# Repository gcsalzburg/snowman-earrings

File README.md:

# ⛄ Snowman Earrings

An experiment in using the ATtiny85 and ISP programming.

## Design

| Pin | Function | Programming |
| --- | --- | --- |
| 0 | Push switch | MOSI |
| 1 | Left eye | MISO |
| 2 | Right eye | SCK |
| 3 | Inner mouth | - |
| 4 | Outer mouth | - |
| 5 | - | RST |

The nose LED is connected permanently to power supply.

+ Micro = [ATTINY85-20SU](https://www.mouser.co.uk/ProductDetail/microchip/attiny85-20su/?qs=8jWQYweyg6N%2FGXnwAe4Icw==&countrycode=DE&currencycode=EUR) 
+ LED = [Broadcom HSMA-C170-T0000](https://www.mouser.co.uk/ProductDetail/broadcom-limited/hsma-c170-t0000/?qs=tMOYG%252bw4%252bLzJIEVH84X7hQ==&countrycode=DE&currencycode=EUR)
+ Switch = [Omron B3U-1000P](https://www.mouser.co.uk/ProductDetail/omron/b3u-1000p/?qs=AO7BQMcsEu4ip80xyf2FwA==&countrycode=DE&currencycode=EUR)
+ Battery holder = [Keystone 3002](https://www.mouser.co.uk/ProductDetail/keystone-electronics/3002/?qs=Mn60vILZNNZWJpgHXc3g8Q==&countrycode=DE&currencycode=EUR)  
+ Power supply = CR2032 battery

## How to program

1. Upload the sketch `File > Examples > 11.ArduinoISP > ArduinoISP` to Arduino Uno.
2. Wire up UNO as shown below:

   | What | Uno | ATtiny85 |
   | --- | --- | --- |
   | 5V  | Vcc | Vcc |
   | Gnd | Gnd | Gnd |
   | SCK | Pin 13 | Pin 2 |
   | MISO | Pin 13 | Pin 1 |
   | MOSI | Pin 13 | Pin 0 |
   | RST | Pin 13 | Reset |

	Also add a 10μF capacitor between Uno RESET and GND, to avoid Arduino being auto reset when uploading to ATtiny85. This goes in backwards (i.e. anode of capacitor is in GND of Uno).

3. In Arduino IDE, select ATtiny85 from `Tools > Board` menu. See Clock to `8MHz (internal)`  (note that ATTiny85 default is 1MHz). If not found, install `attiny by Davis A. Mellis` boards in `Board Manager`. 

3. Select `Arduino as ISP` in `Tools > Programmer`.

3. Burn bootloader to ATtiny85 using `Tools > Burn Bootloader`

3. Now in `VSCode`, set COM port of Arduino Uno in PlatformIO project in `platformio.ini` and upload! If having problems, can also try using [Arduino IDE to upload](https://create.arduino.cc/projecthub/arjun/programming-attiny85-with-arduino-uno-afb829).

## Board design

A few views of the board, for reference:

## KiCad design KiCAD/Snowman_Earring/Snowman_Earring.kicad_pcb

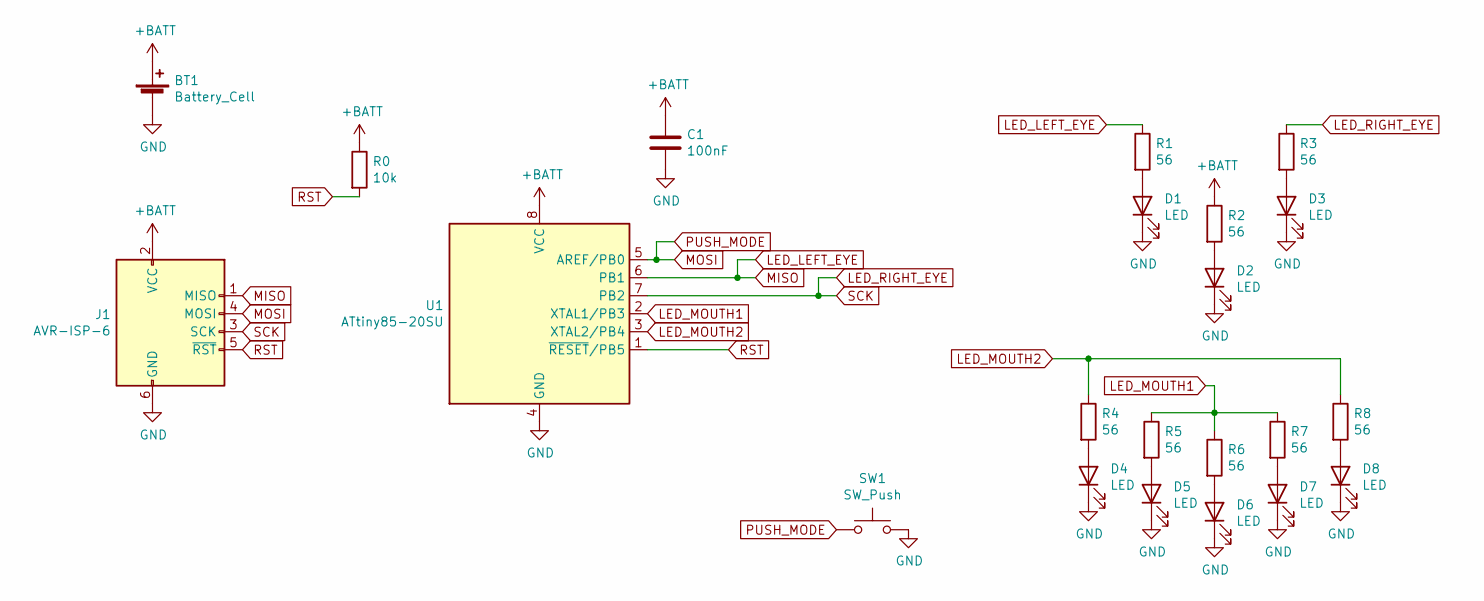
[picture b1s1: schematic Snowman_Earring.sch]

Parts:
BT1: Battery_Cell; BatteryHolder_Keystone_3002_1x2032
C1: 100nF; C_0805_2012Metric_Pad1.15x1.40mm_HandSolder
D1, D2, D3, D4, D5, D6, D7, D8: LED; LED_0805_2012Metric_Pad1.15x1.40mm_HandSolder
J1: AVR-ISP-6; PinHeader_2x03_P2.54mm_Vertical
R0: 10k; R_0805_2012Metric_Pad1.15x1.40mm_HandSolder
R1, R2, R3, R4, R5, R6, R7, R8: 56; R_0805_2012Metric_Pad1.15x1.40mm_HandSolder
SW1: SW_Push; SW_SPST_B3U-1000P
U1: ATtiny85-20SU; SOIJ-8_5.3x5.3mm_P1.27mm

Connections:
+BATT: BT1.1 (+), C1.1, J1.2 (VCC), R0.1, R2.1, U1.8 (VCC)
GND: BT1.2 (-), C1.2, D1.1 (K), D2.1 (K), D3.1 (K), D4.1 (K), D5.1 (K), D6.1 (K), D7.1 (K), D8.1 (K), J1.6 (GND), SW1.2, U1.4 (GND)
LED_LEFT_EYE: J1.1 (MISO), R1.1, U1.6 (PB1)
LED_MOUTH1: R5.1, R6.1, R7.1, U1.2 (XTAL1/PB3)
LED_MOUTH2: R4.1, R8.1, U1.3 (XTAL2/PB4)
LED_RIGHT_EYE: J1.3 (SCK), R3.1, U1.7 (PB2)
MOSI: J1.4 (MOSI), SW1.1, U1.5 (AREF/PB0)
unnamed: D1.2 (A), R1.2
unnamed: D2.2 (A), R2.2
unnamed: D3.2 (A), R3.2
unnamed: D4.2 (A), R4.2
unnamed: D5.2 (A), R5.2
unnamed: D6.2 (A), R6.2
unnamed: D7.2 (A), R7.2
unnamed: D8.2 (A), R8.2
RST: J1.5 (~RST), R0.2, U1.1 (~RESET~/PB5)

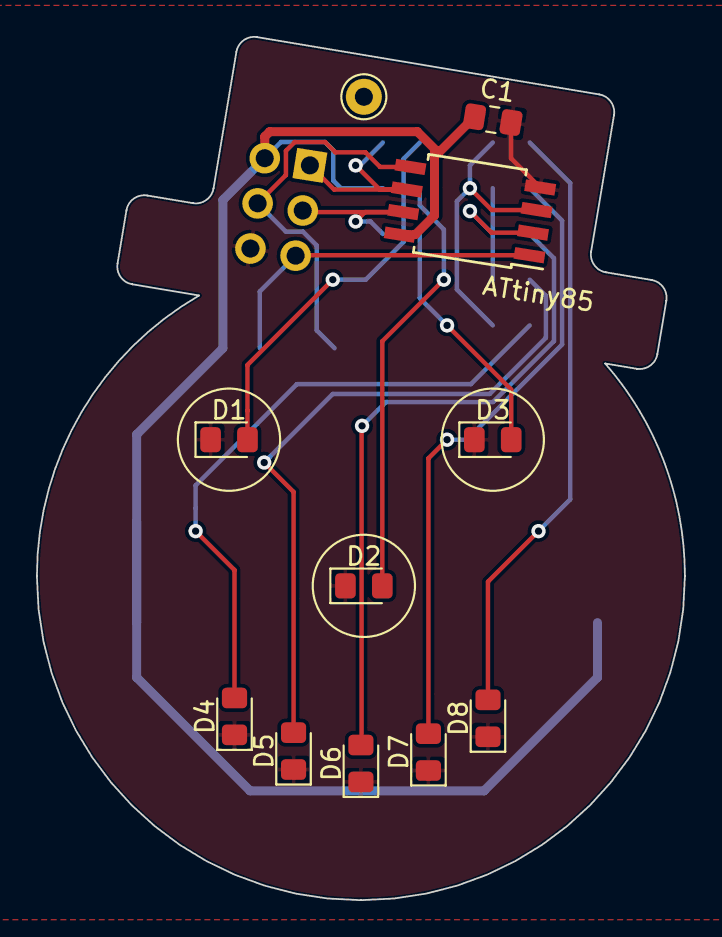
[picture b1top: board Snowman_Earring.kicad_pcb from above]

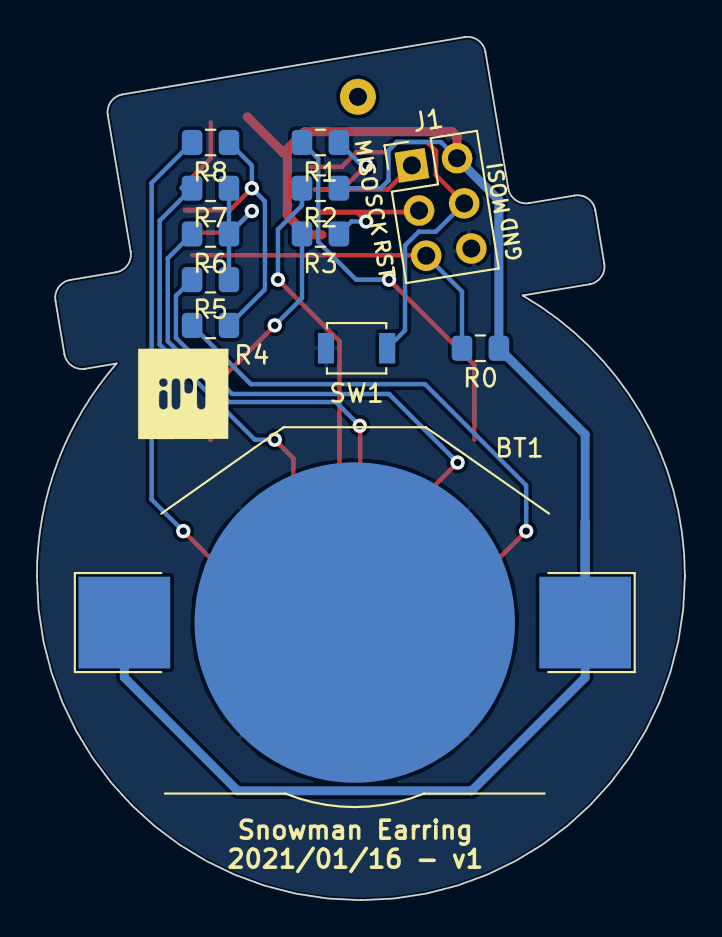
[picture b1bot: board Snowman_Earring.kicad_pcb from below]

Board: 2 copper layers, 36.0 x 48.0 mm, 22 parts (12 on the bottom side), 16 nets.

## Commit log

2021-02-09 Add platfomio boilerplate
2021-02-09 Basic flashing test
2021-02-10 Add switch and animation loop
2021-02-11 Update sequence
2021-12-10 Update COM port
2021-12-10 Add new sequences
2021-12-11 Add KiCAD files
2021-12-11 Add image of layout
2021-12-11 Add images and readme
2021-12-11 Set theme jekyll-theme-midnight
2021-12-11 Add images
2021-12-11 Fill in table for ATtiny85
2021-12-11 Remove default Jekyll theme
2022-09-02 Update image linked location
